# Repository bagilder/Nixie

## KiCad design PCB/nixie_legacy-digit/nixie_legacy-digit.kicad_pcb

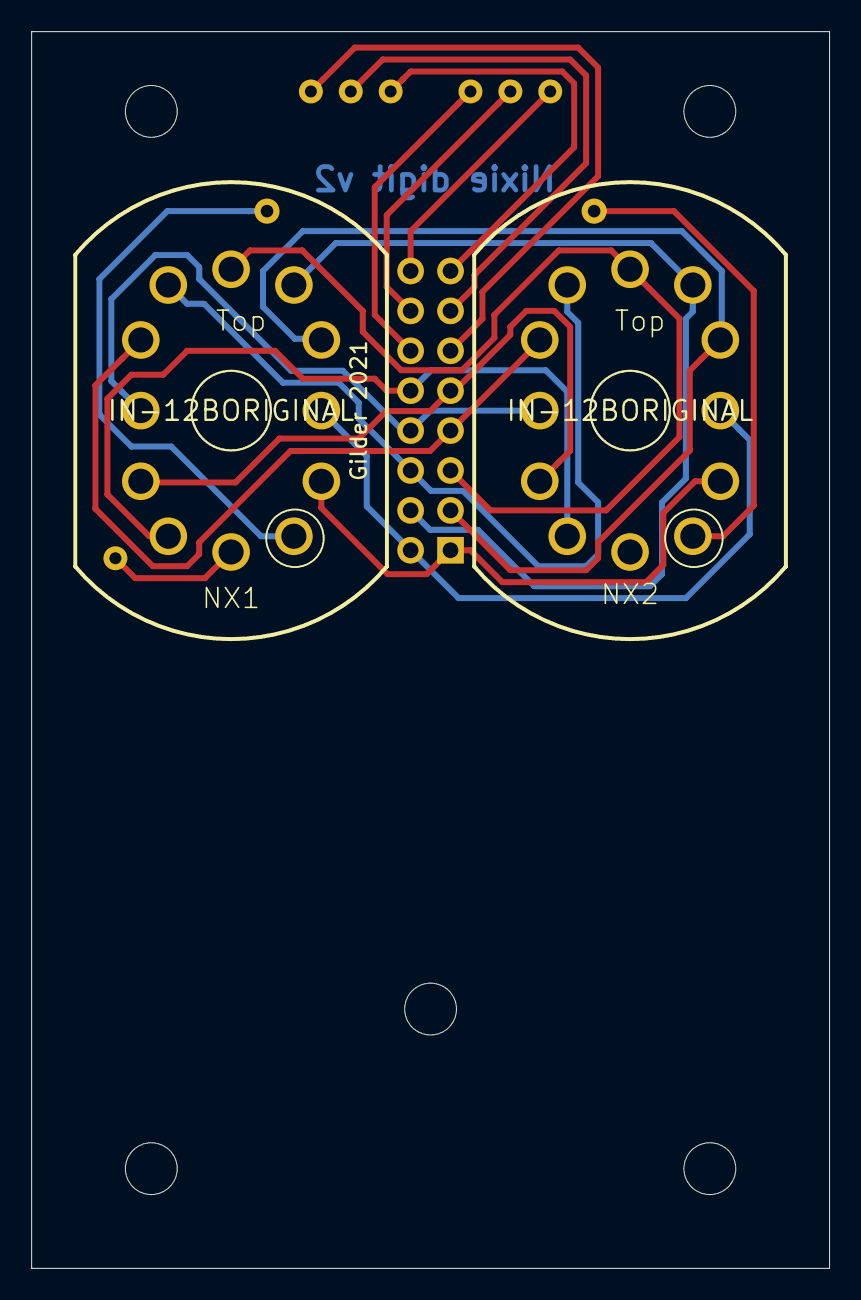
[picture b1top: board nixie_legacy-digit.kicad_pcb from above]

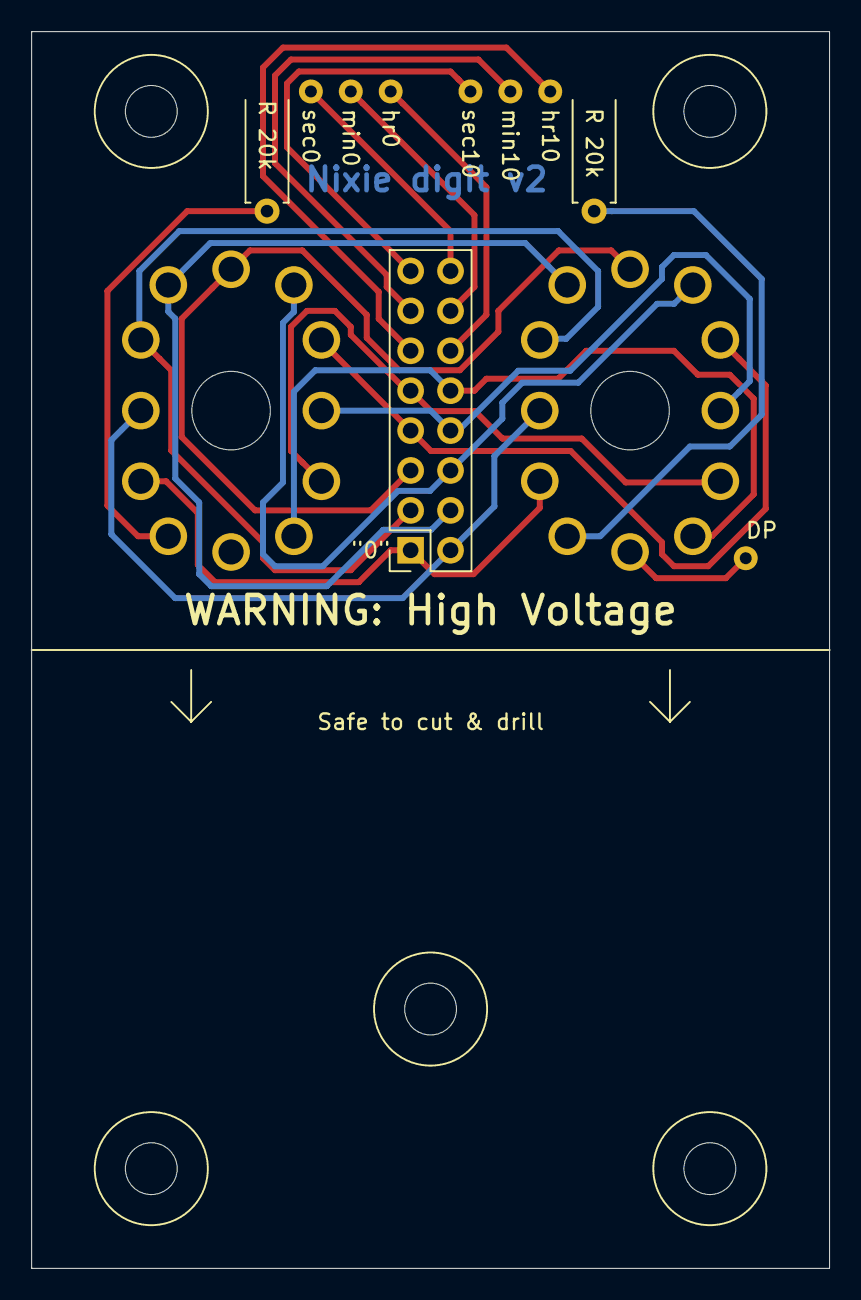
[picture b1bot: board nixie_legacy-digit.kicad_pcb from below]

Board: 2 copper layers, 50.8 x 78.7 mm, 12 parts (8 on the bottom side), 19 nets.

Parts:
"0": HEADER_16; PinHeader_2x08_P2.54mm_Vertical
DP: HEADER_1; Single_pad-1x1
NX1, NX2: IN-12BORIGINAL; nixies-us-IN-12-DSUB
R 20k, R 20k#2: 20k; R_Axial_DIN0207_L6.3mm_D2.5mm_P7.62mm_Horizontal
hr0, hr10: HEADER_1; Single_pad-1x1
min0, min10: HEADER_1; Single_pad-1x1
sec0, sec10: HEADER_1; Single_pad-1x1

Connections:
0: "0".2, NX1.0, NX2.0
1: "0".9, NX1.1, NX2.1
2: "0".10, NX1.2, NX2.2
3: "0".7, NX1.3, NX2.3
4: "0".8, NX1.4, NX2.4
5: "0".5, NX1.5, NX2.5
6: "0".6, NX1.6, NX2.6
7: "0".3, NX1.7, NX2.7
8: "0".4, NX1.8, NX2.8
9: "0".1, NX1.9, NX2.9
unnamed: NX1.A, R 20k#2.2
unnamed: DP.1, NX1.LHDP
unnamed: NX2.A, R 20k.2
digit1msb: "0".12, hr10.1
digit2: "0".11, hr0.1
digit3: "0".14, min10.1
digit4: "0".13, min0.1
digit5: "0".16, sec10.1
digit6lsb: "0".15, sec0.1

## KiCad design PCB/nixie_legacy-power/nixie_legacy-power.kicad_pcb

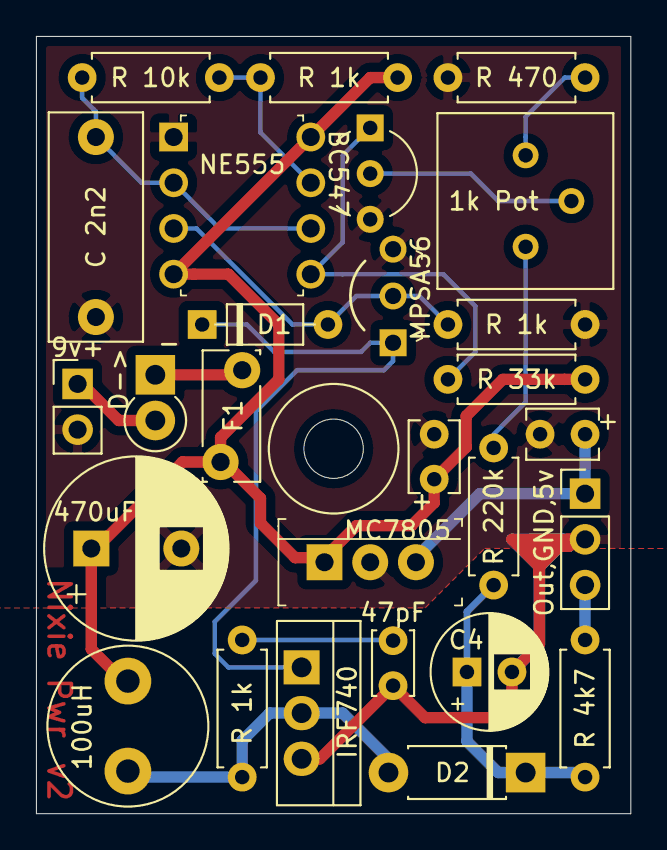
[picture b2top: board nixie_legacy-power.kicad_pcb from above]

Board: 2 copper layers, 33.0 x 43.2 mm, 27 parts (0 on the bottom side), 17 nets.

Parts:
1k Pot: 1k; Potentiometer_Bourns_3386P_Vertical
5v: 220nTANT; C_Disc_D3.8mm_W2.6mm_P2.50mm
9v+: Barrel_Jack; PinHeader_1x02_P2.54mm_Vertical
47pF: 47p; C_Disc_D3.4mm_W2.1mm_P2.50mm
100uH: 100u; L_Radial_D8.7mm_P5.00mm_Fastron_07HCP
470uF: 470u; CP_Radial_D10.0mm_P5.00mm
+: 220nTANT; C_Disc_D3.8mm_W2.6mm_P2.50mm
BC547: BC547; TO-92_Inline_Wide
C4: 1u; CP_Radial_D6.3mm_P2.50mm
C 2n2: 2.2n; C_Disc_D12.5mm_W5.0mm_P10.00mm
D1: D_ALT; D_DO-35_SOD27_P7.62mm_Horizontal
D2: D; D_DO-41_SOD81_P7.62mm_Horizontal
D->: D; D_DO-41_SOD81_P2.54mm_Vertical_KathodeUp
F1: Polyfuse; Fuse_Bourns_MF-RG300
IRF740: IRF740; TO-220-3_Vertical
MC7805: MC7805CT-BP; TO-220-3
MPSA56: MPSA56-AP; TO-92-3_Formed_Leads
NE555: NE555P; DIP-8_W7.62mm
Out,GND,: HEADER_3; PinHeader_1x03_P2.54mm_Vertical
R 1k, R 1k#2, R 1k#3: 1k; R_Axial_DIN0207_L6.3mm_D2.5mm_P7.62mm_Horizontal
R 4k7: 4.7k; R_Axial_DIN0207_L6.3mm_D2.5mm_P7.62mm_Horizontal
R 10k: 10k; R_Axial_DIN0207_L6.3mm_D2.5mm_P7.62mm_Horizontal
R 33k: 33k; R_Axial_DIN0207_L6.3mm_D2.5mm_P7.62mm_Horizontal
R 220k: 220k; R_Axial_DIN0207_L6.3mm_D2.5mm_P7.62mm_Horizontal
R 470: 470; R_Axial_DIN0207_L6.3mm_D2.5mm_P7.62mm_Horizontal

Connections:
5v: 5v.1, MC7805.3, Out,GND,.1
9v: 100uH.1, 470uF.1, +.1, F1.2, MC7805.1, NE555.4, NE555.8, R 1k#3.2, R 33k.1
GND: 5v.2, 9v+.2, 47pF.2, 470uF.2, +.2, BC547.3, C4.2, C 2n2.2, IRF740.3, MC7805.2, MPSA56.3, NE555.1, Out,GND,.2, R 1k#2.2, R 470.2
unnamed: C 2n2.1, NE555.2, NE555.6, R 10k.1
unnamed: 47pF.1, R 1k.2
unnamed: C4.1, D2.1, R 4k7.2, R 220k.2
unnamed: D1.1, IRF740.1, MPSA56.1
unnamed: D1.2, MPSA56.2, NE555.3, R 1k#2.1
unnamed: 100uH.2, D2.2, IRF740.2, R 1k.1
unnamed: D->.1, F1.1
unnamed: 9v+.1, D->.2
unnamed: BC547.1, NE555.5, R 33k.2
unnamed: 1k Pot.2, BC547.2
unnamed: NE555.7, R 1k#3.1, R 10k.2
unnamed: 1k Pot.1, R 220k.1
unnamed: 1k Pot.3, R 470.1
output: Out,GND,.3, R 4k7.1

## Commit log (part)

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2021-07-25 rebaslining
2021-07-25 Added PCB files
2021-07-25 Rebaslining "production" legacy code
2021-07-26 Fixing analog pin conflict for random seed (future-proofing)
2021-07-31 updated NIXIE_LEGACY_CODE.cpp to use uint8 instead of int in most of the extraneous cases
2021-07-31 updated NIXIE_LEGACY_CODE.cpp to uint8_t from int in most of the extraneous cases. if this is a double push, i missed a few last time
2021-07-31 added i2c_rtc_test.c to test interfacing with RX8025 rtc module
2021-07-31 added new_rtc.cpp to integrate legacy mux code with new rtc timekeeping. this commit contains only the i2c control to interface with the rtc module
2021-07-31 integrating legacy code into new_rtc.cpp. yet untested on hardware, but compiles
2021-08-05 new_rtc.cpp now generally works on hardware. added pullup resistor to /inta to prevent ping spamming. bugs remaining in time set, especially switching 12/24 hr
2021-08-06 Updating power PCB to v2 to include 5v regulator and support post hole
2021-08-06 Demux circuit schematic now complete with RTC (including 1Hz interrupt pin)
2021-08-06 new_rtc.cpp moved digit bcd pin4 to digital pin 0 (which has a conflict with Rx but this won't matter if serial comm is turned off) to stay away from port c and keep all on same side of chip. have no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
2021-08-06 Demux pcb rough layout blocking. no routing yet
2021-08-07 Adding demux PCB v1: uses resistor network for 100k, has npn on board but pnp is on digit board
2021-08-07 Schematic of digit board v1: pnp on board
2021-08-08 power pcb updated. wrote my name on the silk screen :)
2021-08-08 demux pcb v2, has MPSA92 transistors on this board instead of digit board, reducing connector to 16 pins instead of 18.
2021-08-08 digit pcb v1. extra long so that it can fit in my specific clock enclosure. made a "safe to cut" zone so it can be shortened for other applications
2021-08-08 digit pcb updated. added breakout for left decimal point (for 4-digit clocks)
2021-08-10 demux pcb update: footprint for rtc was sop 16 instead of sop 14. rerouted power traces. shortened to 3.75"
2021-08-12 power pcb. added input polarity protection diode and rearranged board to fit accordingly. removed ground plane from high voltage zone. (recommit)
2021-08-19 digit pcb update. removed flood fill copper
2021-08-19 all PCB gerbers zip add/update
2021-09-01 SR_drive_test.c initial commit. allows testing a pair of tubes using 74hc595 shift registers by repurposing the SPI pins. directly driving each tube, two tubes per 595
2021-09-03 SR_drive_test.c updated to include final blanking stage. changed to support power demux of the pairs if the data outputs of the SR are bussed between digits
2021-09-03 SR_drive_test.c updated with toggle variable to allow either bussed data or direct drive digit configuration
2021-09-05 SR_drive_test.c future proofed to support 3-to-8 mux to distribute latch pin for eventual distribution of serial data. also fixed ghosting issue and blanking timing on pair demux scheme
2021-11-17 -power board: updated 7805 footprint to better fit piece, "A55" instead of "A56", 9v input pad shape swap so that ground makes sense -digit board: added resistor value, vertical connector, correct pi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
2023-03-08 new_rtc: tried and failed to fix hour roll animation
2023-03-08 new_rtc: set looper magicnumber had uint underflow, needed int. still resets to :12 at roll for some reason tho
2023-05-18 new_rtc: squished 24hr fancy roll animation bug. 24hr should now be functional. -only fancy roll animation active, haven't looked at 12hr bugs but who cares
2023-05-18 new_rtc: fixed tube ghosting by turning off serial debugging you dummy. 24hr gucci
2025-08-01 SR baseline: redesign for shift registers. written but untested
2025-08-01 SR baseline: added hour transition animation. compiles but still untested
2025-08-01 SR baseline: perhaps a slightly more janky yet more gooderer wait_for_set function. still untested
2025-08-21 add ino - focusing on this file going forward. cpp file ignored from here tbh
2025-08-21 SR ino: all 3 digit sets display correctly. hour animate works.
2025-08-21 SR ino: settings menu appears to be working. includes an option to set brightness but no display during, and haven't incorporated functionality in main send function
2025-08-21 SR ino: i think...... i have all basic functionality complete??? i think only brightness setting remains? what the heck
2026-03-31 nixie SR: fixed hour set bug. animate starts at top of :59 instead of at rollover
